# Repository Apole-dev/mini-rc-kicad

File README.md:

# mini-rc-kicad
## Schematic

## PCB

## 3D Modeling

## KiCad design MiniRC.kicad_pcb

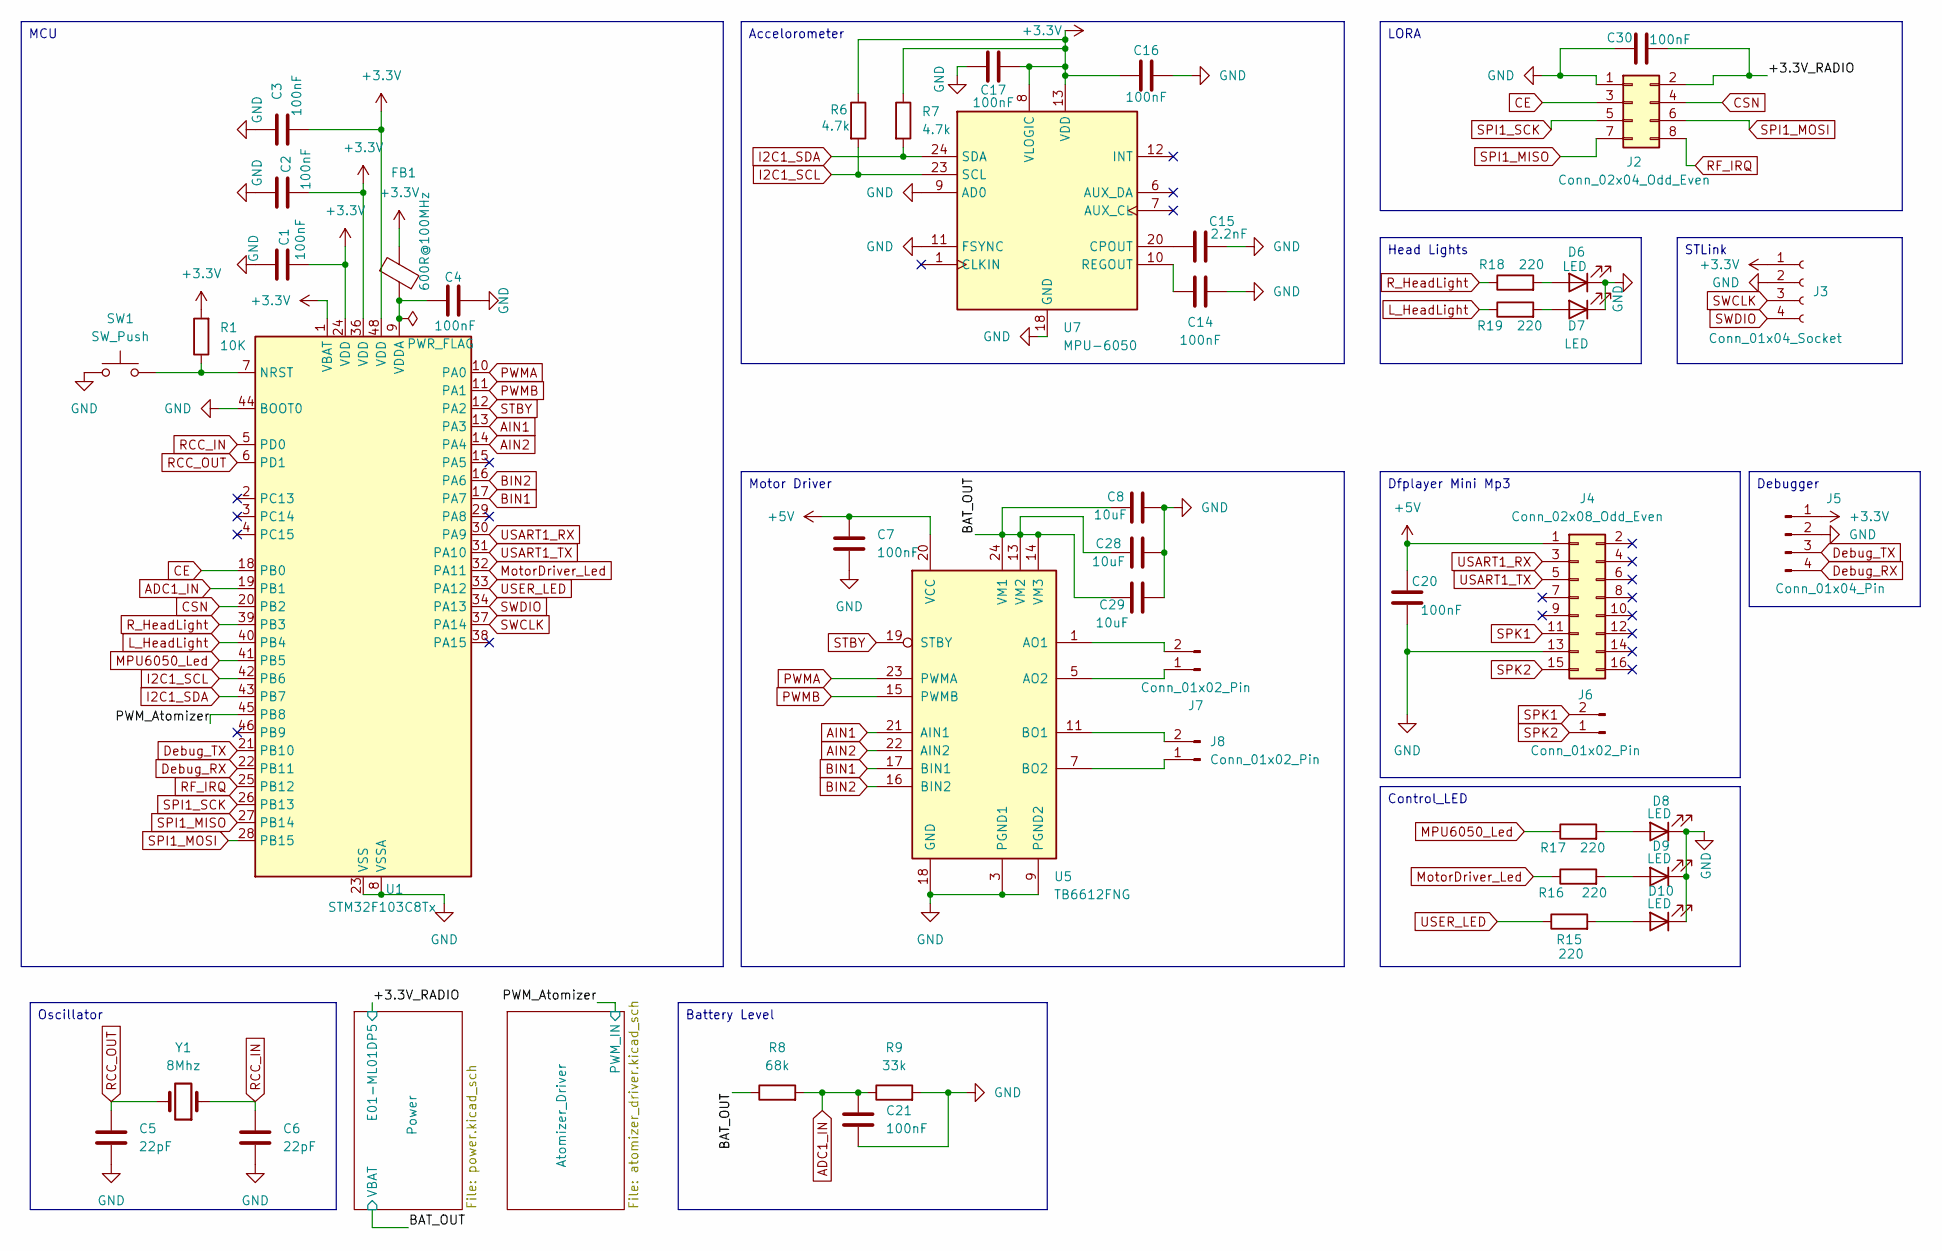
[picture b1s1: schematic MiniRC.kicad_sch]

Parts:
C1, C2, C3, C4, C7, C14, C16, C17, C20, C21, C30: 100nF; C_0805_2012Metric_Pad1.18x1.45mm_HandSolder
C5, C6: 22pF; C_0805_2012Metric_Pad1.18x1.45mm_HandSolder
C8, C28, C29: 10uF; C_0805_2012Metric_Pad1.18x1.45mm_HandSolder
C15: 2.2nF; C_0805_2012Metric_Pad1.18x1.45mm_HandSolder
D6, D7, D8, D9, D10: LED; LED_0805_2012Metric_Pad1.15x1.40mm_HandSolder
FB1: 600R@100MHz; R_0805_2012Metric
J2: Conn_02x04_Odd_Even; PinHeader_2x04_P2.54mm_Vertical
J3: Conn_01x04_Socket; PinHeader_1x04_P2.54mm_Vertical
J4: Conn_02x08_Odd_Even; PinHeader_2x08_P2.54mm_Vertical
J5: Conn_01x04_Pin; PinHeader_1x04_P2.54mm_Vertical
J6: Conn_01x02_Pin; SolderWire-1.5sqmm_1x02_P7.8mm_D1.7mm_OD3.9mm
J7, J8: Conn_01x02_Pin; SolderWire-0.75sqmm_1x02_P7mm_D1.25mm_OD3.5mm
R1: 10K; R_0805_2012Metric_Pad1.20x1.40mm_HandSolder
R6, R7: 4.7k; R_0805_2012Metric_Pad1.20x1.40mm_HandSolder
R8: 68k; R_0805_2012Metric_Pad1.20x1.40mm_HandSolder
R9: 33k; R_0805_2012Metric_Pad1.20x1.40mm_HandSolder
R15, R16, R17, R18, R19: 220; R_0805_2012Metric_Pad1.20x1.40mm_HandSolder
SW1: SW_Push; SW_Push_1P1T_NO_CK_KMR2
U1: STM32F103C8Tx; LQFP-48_7x7mm_P0.5mm
U5: TB6612FNG; SSOP-24_5.3x8.2mm_P0.65mm
U7: MPU-6050; InvenSense_QFN-24_4x4mm_P0.5mm
Y1: 8Mhz; Crystal_SMD_HC49-SD

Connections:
+3.3V: C1.2, C2.1, C3.2, C16.1, C17.1, FB1.1, J3.1, J5.1, R1.2, R6.1, R7.1, U1.1 (VBAT), U1.24 (VDD), U1.36 (VDD), U1.48 (VDD), U7.8 (VLOGIC), U7.13 (VDD); also elsewhere on the board
+5V: C7.1, C20.1, J4.1, U5.20 (VCC); also elsewhere on the board
/+3.3V_RADIO: C30.2, J2.2; also elsewhere on the board
/BAT_OUT: C8.1, C28.1, C29.1, R8.1, U5.13 (VM2), U5.14 (VM3), U5.24 (VM1); also elsewhere on the board
/PWM_Atomizer: U1.45 (PB8); also elsewhere on the board
ADC1_IN: C21.1, R8.2, R9.1, U1.19 (PB1)
AIN1: U1.13 (PA3), U5.21 (AIN1)
AIN2: U1.14 (PA4), U5.22 (AIN2)
BIN1: U1.17 (PA7), U5.17 (BIN1)
BIN2: U1.16 (PA6), U5.16 (BIN2)
CE: J2.3, U1.18 (PB0)
CSN: J2.4, U1.20 (PB2)
Debug_RX: J5.4, U1.22 (PB11)
Debug_TX: J5.3, U1.21 (PB10)
GND: C1.1, C2.2, C3.1, C4.2, C5.2, C6.2, C7.2, C8.2, C14.2, C15.2, C16.2, C17.2, C20.2, C21.2, C28.2, C29.2, C30.1, D6.1 (K), D7.1 (K), D8.1 (K), D9.1 (K), D10.1 (K), J2.1, J3.2, J4.13, J5.2, R9.2, SW1.1, U1.8 (VSSA), U1.23 (VSS), U1.35 (VSS), U1.44 (BOOT0), U1.47 (VSS), U5.3 (PGND1), U5.4 (PGND1), U5.9 (PGND2), U5.10 (PGND2), U5.18 (GND), U7.9 (AD0), U7.11 (FSYNC), U7.18 (GND); also elsewhere on the board
I2C1_SCL: R6.2, U1.42 (PB6), U7.23 (SCL)
I2C1_SDA: R7.2, U1.43 (PB7), U7.24 (SDA)
L_HeadLight: R19.1, U1.40 (PB4)
MPU6050_Led: R17.1, U1.41 (PB5)
MotorDriver_Led: R16.1, U1.32 (PA11)
unnamed: D6.2 (A), R18.2
unnamed: D7.2 (A), R19.2
unnamed: D8.2 (A), R17.2
unnamed: D9.2 (A), R16.2
unnamed: D10.2 (A), R15.2
unnamed: J7.1, U5.5 (AO2), U5.6 (AO2)
unnamed: J7.2, U5.1 (AO1), U5.2 (AO1)
unnamed: J8.1, U5.7 (BO2), U5.8 (BO2)
unnamed: J8.2, U5.11 (BO1), U5.12 (BO1)
unnamed: R1.1, SW1.2, U1.7 (NRST)
unnamed: C4.1, FB1.2, U1.9 (VDDA)
unnamed: C15.1, U7.20 (CPOUT)
unnamed: C14.1, U7.10 (REGOUT)
PWMA: U1.10 (PA0), U5.23 (PWMA)
PWMB: U1.11 (PA1), U5.15 (PWMB)
RCC_IN: C6.1, U1.5 (PD0), Y1.1
RCC_OUT: C5.1, U1.6 (PD1), Y1.2
RF_IRQ: J2.8, U1.25 (PB12)
R_HeadLight: R18.1, U1.39 (PB3)
SPI1_MISO: J2.7, U1.27 (PB14)
SPI1_MOSI: J2.6, U1.28 (PB15)
SPI1_SCK: J2.5, U1.26 (PB13)
SPK1: J4.11, J6.2
SPK2: J4.15, J6.1
STBY: U1.12 (PA2), U5.19 (STBY)
SWCLK: J3.3, U1.37 (PA14)
SWDIO: J3.4, U1.34 (PA13)
USART1_RX: J4.3, U1.30 (PA9)
USART1_TX: J4.5, U1.31 (PA10)
USER_LED: R15.1, U1.33 (PA12)

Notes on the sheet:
Accelorometer
Head Lights
MCU
Dfplayer Mini Mp3
Control_LED
Debugger
STLink
Oscillator
Battery Level
LORA
Motor Driver

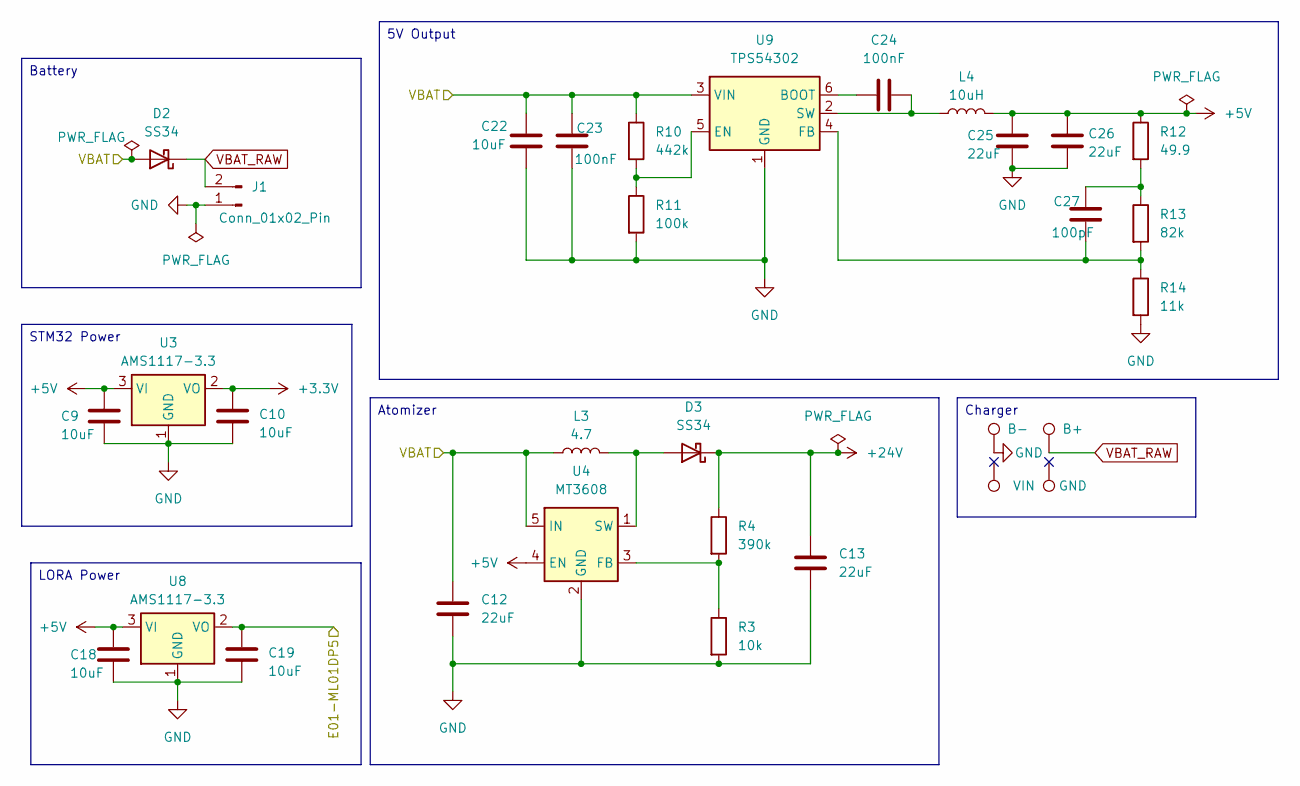
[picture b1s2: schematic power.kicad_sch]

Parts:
C9, C10, C18, C19, C22: 10uF; C_0805_2012Metric_Pad1.18x1.45mm_HandSolder
C12, C13, C25, C26: 22uF; C_0805_2012Metric_Pad1.18x1.45mm_HandSolder
C23, C24: 100nF; C_0805_2012Metric_Pad1.18x1.45mm_HandSolder
C27: 100pF; C_0805_2012Metric_Pad1.18x1.45mm_HandSolder
D2, D3: SS34; D_SMC_Handsoldering
J1: Conn_01x02_Pin; SolderWire-1.5sqmm_1x02_P7.8mm_D1.7mm_OD3.9mm
L3: 4.7; L_7.3x7.3_H4.5
L4: 10uH; L_7.3x7.3_H4.5
R3: 10k; R_0805_2012Metric_Pad1.20x1.40mm_HandSolder
R4: 390k; R_0805_2012Metric_Pad1.20x1.40mm_HandSolder
R10: 442k; R_0805_2012Metric_Pad1.20x1.40mm_HandSolder
R11: 100k; R_0805_2012Metric_Pad1.20x1.40mm_HandSolder
R12: 49.9; R_0805_2012Metric_Pad1.20x1.40mm_HandSolder
R13: 82k; R_0805_2012Metric_Pad1.20x1.40mm_HandSolder
R14: 11k; R_0805_2012Metric_Pad1.20x1.40mm_HandSolder
TP1: B-; TestPoint_Pad_D2.0mm
TP2: VIN; TestPoint_Pad_D2.0mm
TP3: B+; TestPoint_Pad_D2.0mm
TP4: GND; TestPoint_Pad_D2.0mm
U3, U8: AMS1117-3.3; SOT-223-3_TabPin2
U4: MT3608; SOT-23-6
U9: TPS54302; SOT-23-6

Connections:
+3.3V: C10.1, U3.2 (VO); also elsewhere on the board
+5V: C9.1, C18.1, C25.1, C26.1, L4.2, R12.1, U3.3 (VI), U4.4 (EN), U8.3 (VI); also elsewhere on the board
+24V: C13.1, D3.1 (K), R4.1; also elsewhere on the board
/+3.3V_RADIO: C19.1, U8.2 (VO); also elsewhere on the board
/BAT_OUT: C12.1, C22.1, C23.1, D2.2 (A), L3.1, R10.1, U4.5 (IN), U9.3 (VIN); also elsewhere on the board
GND: C9.2, C10.2, C12.2, C13.2, C18.2, C19.2, C22.2, C23.2, C25.2, C26.2, J1.1, R3.2, R11.2, R14.2, TP1.1, U3.1 (GND), U4.2 (GND), U8.1 (GND), U9.1 (GND); also elsewhere on the board
unnamed: C27.1, R12.2, R13.1
unnamed: D3.2 (A), L3.2, U4.1 (SW)
unnamed: R3.1, R4.2, U4.3 (FB)
unnamed: C24.2, U9.6 (BOOT)
unnamed: R10.2, R11.1, U9.5 (EN)
unnamed: C27.2, R13.2, R14.1, U9.4 (FB)
unnamed: C24.1, L4.1, U9.2 (SW)
VBAT_RAW: D2.1 (K), J1.2, TP3.1

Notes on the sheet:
5V Output
STM32 Power
Charger
Battery
LORA Power
Atomizer

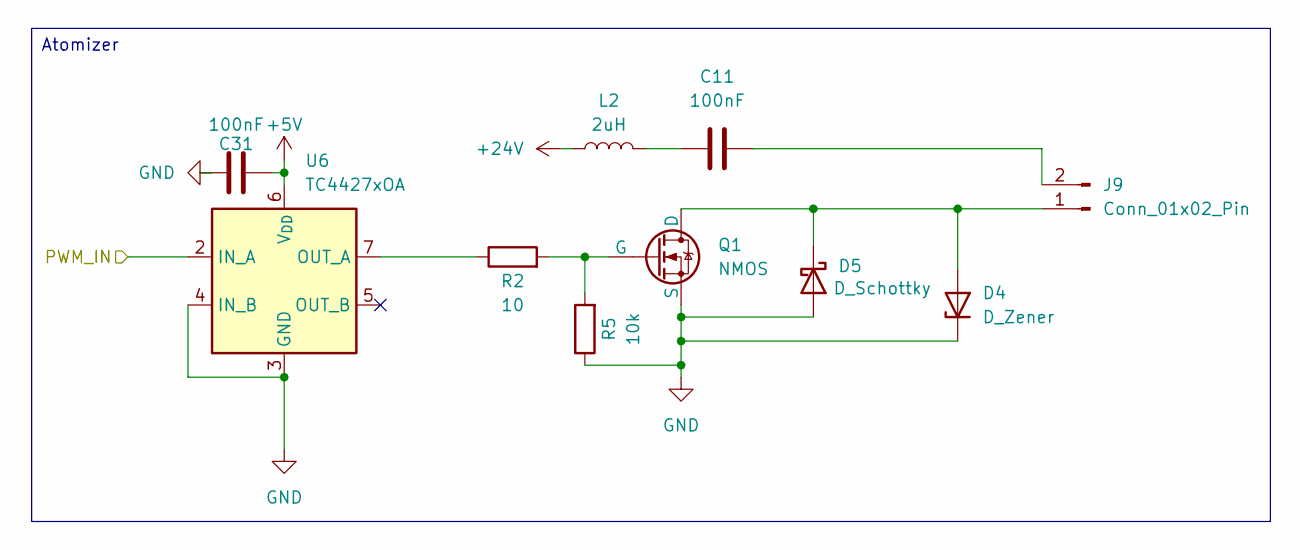
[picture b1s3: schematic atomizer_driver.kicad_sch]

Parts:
C11: 100nF; C_Disc_D10.5mm_W5.0mm_P10.00mm
C31: 100nF; C_0805_2012Metric_Pad1.18x1.45mm_HandSolder
D4: D_Zener; D_SMA_Handsoldering
D5: D_Schottky; D_SMA_Handsoldering
J9: Conn_01x02_Pin; SolderWire-1.5sqmm_1x02_P7.8mm_D1.7mm_OD3.9mm
L2: 2uH; L_1206_3216Metric_Pad1.22x1.90mm_HandSolder
Q1: NMOS; TO-252-2
R2: 10; R_0805_2012Metric_Pad1.20x1.40mm_HandSolder
R5: 10k; R_0805_2012Metric_Pad1.20x1.40mm_HandSolder
U6: TC4427xOA; SOIC-8_3.9x4.9mm_P1.27mm

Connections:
+5V: C31.2, U6.6 (V_{DD}); also elsewhere on the board
+24V: L2.1; also elsewhere on the board
/PWM_Atomizer: U6.2 (IN_A); also elsewhere on the board
GND: C31.1, D4.1 (K), D5.2 (A), Q1.3 (S), R5.1, U6.3 (GND), U6.4 (IN_B); also elsewhere on the board
unnamed: C11.1, L2.2
unnamed: D4.2 (A), D5.1 (K), J9.1, Q1.1 (D)
unnamed: C11.2, J9.2
unnamed: Q1.2 (G), R2.2, R5.2
unnamed: R2.1, U6.7 (OUT_A)

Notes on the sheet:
Atomizer

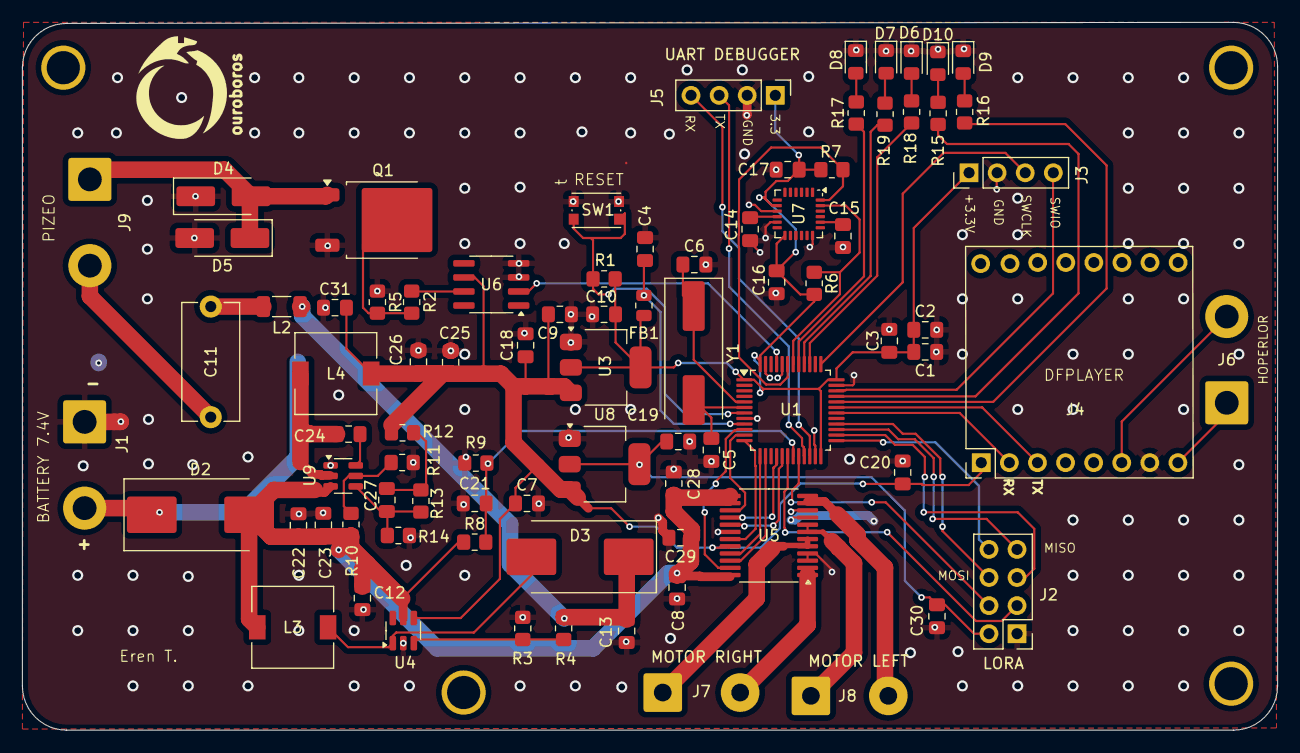
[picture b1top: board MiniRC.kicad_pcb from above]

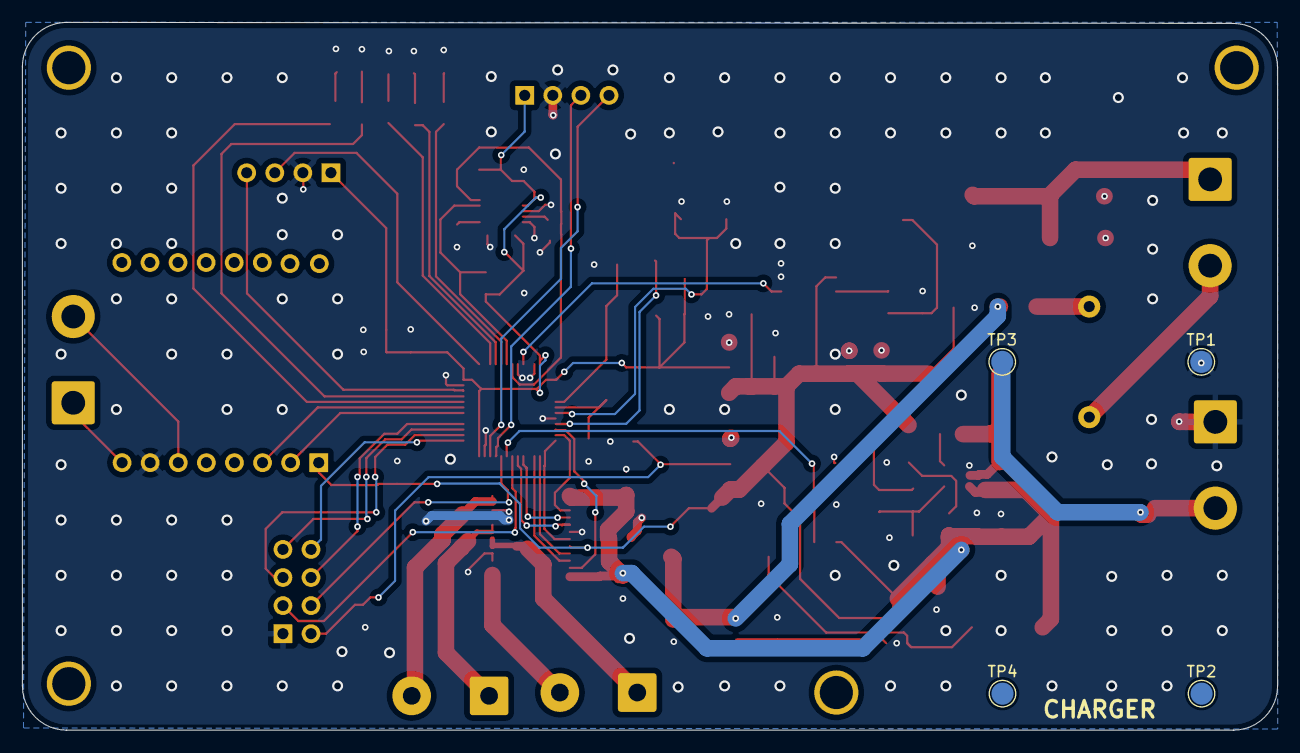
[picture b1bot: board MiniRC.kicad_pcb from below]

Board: 2 copper layers, 113.5 x 64.0 mm, 87 parts (4 on the bottom side), 64 nets.

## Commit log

2025-08-31 Inital Commit
2025-09-01 Organise details
